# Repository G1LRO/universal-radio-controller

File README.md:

# universal-radio-controller
Open Hardware elements of the G1LRO Universal Radio Controller.

Refer to www.g1lro.uk for technical and electronic interface specifications

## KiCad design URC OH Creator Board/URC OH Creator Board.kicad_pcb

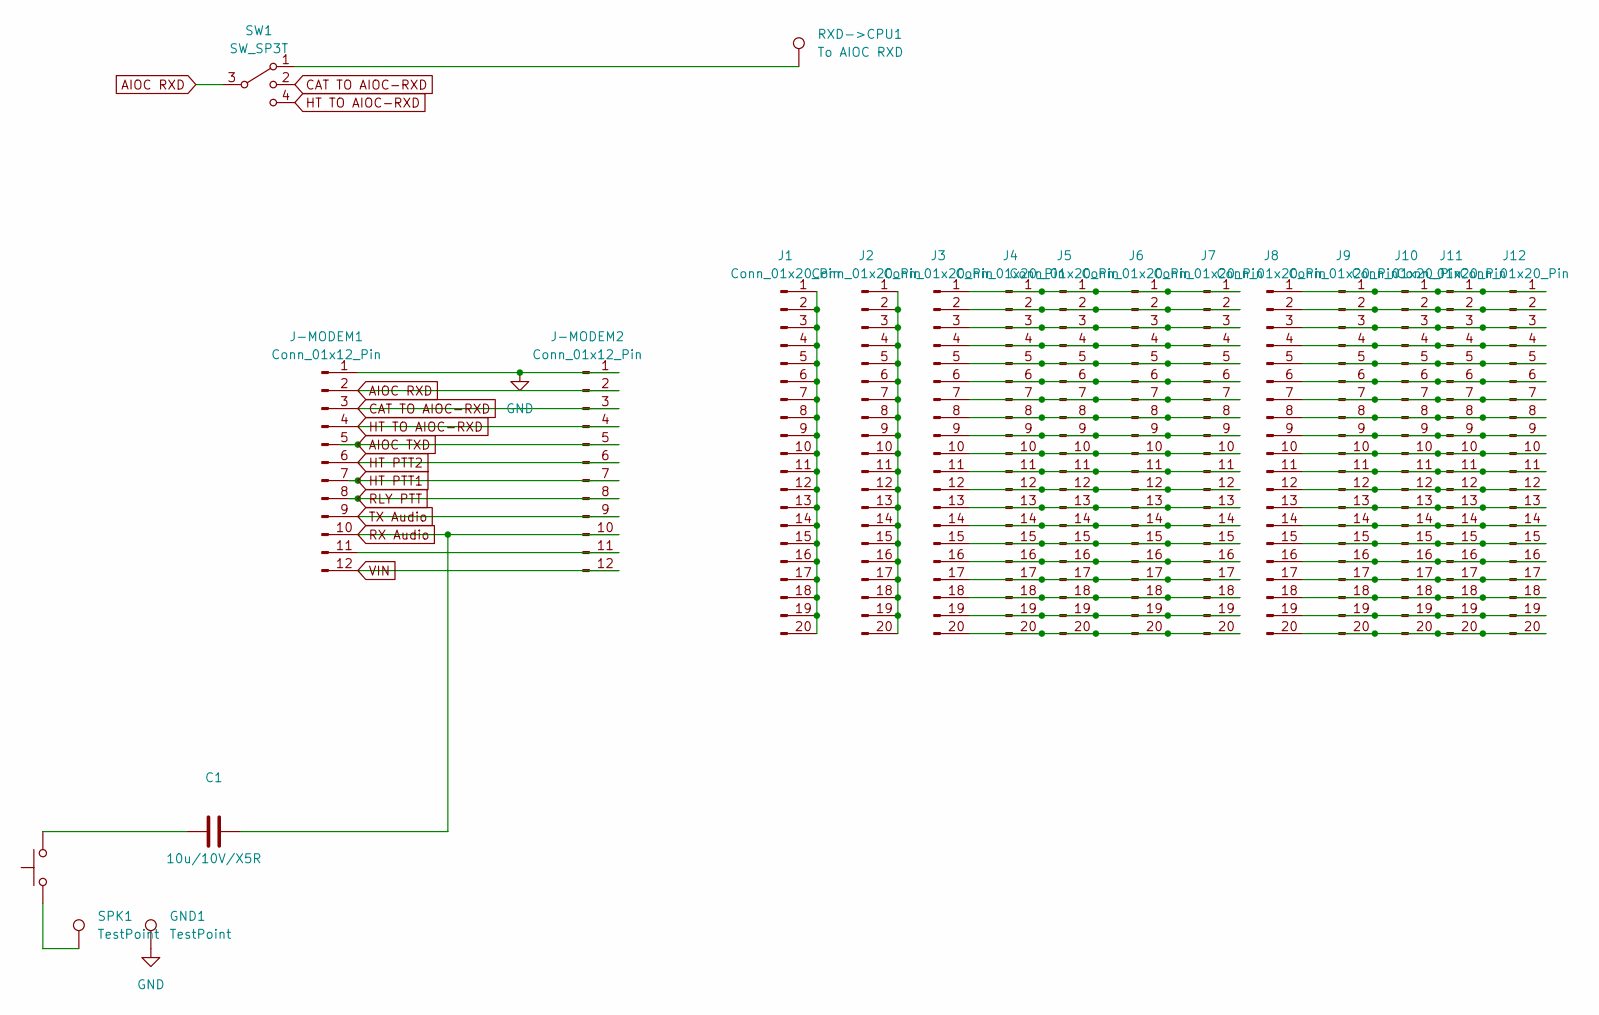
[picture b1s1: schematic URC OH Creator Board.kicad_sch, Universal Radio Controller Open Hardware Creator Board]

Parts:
C1: 10u/10V/X5R; C_0603_1608Metric; LCSC C19702
GND1: TestPoint; TestPoint_Pad_3.0x3.0mm
J1, J2, J3, J4, J5, J6, J7, J8, J9, J10, J11, J12: Conn_01x20_Pin; PinSocket_1x20_P2.54mm_Vertical; LCSC DNP
J-MODEM1, J-MODEM2: Conn_01x12_Pin; PinSocket_1x12_P2.54mm_Vertical; LCSC DNP
RXD->CPU1: To AIOC RXD; TestPoint_THTPad_1.5x1.5mm_Drill0.7mm
SPK1: TestPoint; TestPoint_Pad_3.0x3.0mm
SW1: SW_SP3T; SW_TPDT_THT-5mm; LCSC C393948
SW2: SW Monitor; SW_Tactile_SPST_Angled_C2689823; LCSC C2689823

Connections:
AIOC RXD: J-MODEM1.2, J-MODEM2.2, SW1.3
AIOC TXD: J-MODEM1.5, J-MODEM2.5
CAT TO AIOC-RXD: J-MODEM1.3, J-MODEM2.3, SW1.2
GND: GND1.1, J-MODEM1.1, J-MODEM2.1
HT PTT1: J-MODEM1.7, J-MODEM2.7
HT PTT2: J-MODEM1.6, J-MODEM2.6
HT TO AIOC-RXD: J-MODEM1.4, J-MODEM2.4, SW1.4
unnamed: C1.1, SW2.2
unnamed: J1.1, J1.2, J1.3, J1.4, J1.5, J1.6, J1.7, J1.8, J1.9, J1.10, J1.11, J1.12, J1.13, J1.14, J1.15, J1.16, J1.17, J1.18, J1.19, J1.20
unnamed: J2.1, J2.2, J2.3, J2.4, J2.5, J2.6, J2.7, J2.8, J2.9, J2.10, J2.11, J2.12, J2.13, J2.14, J2.15, J2.16, J2.17, J2.18, J2.19, J2.20
unnamed: J3.1, J4.1, J5.1, J6.1, J7.1
unnamed: J3.2, J4.2, J5.2, J6.2, J7.2
unnamed: J3.3, J4.3, J5.3, J6.3, J7.3
unnamed: J3.4, J4.4, J5.4, J6.4, J7.4
unnamed: J3.5, J4.5, J5.5, J6.5, J7.5
unnamed: J3.6, J4.6, J5.6, J6.6, J7.6
unnamed: J3.7, J4.7, J5.7, J6.7, J7.7
unnamed: J3.8, J4.8, J5.8, J6.8, J7.8
unnamed: J3.9, J4.9, J5.9, J6.9, J7.9
unnamed: J3.10, J4.10, J5.10, J6.10, J7.10
unnamed: J3.11, J4.11, J5.11, J6.11, J7.11
unnamed: J3.12, J4.12, J5.12, J6.12, J7.12
unnamed: J3.13, J4.13, J5.13, J6.13, J7.13
unnamed: J3.14, J4.14, J5.14, J6.14, J7.14
unnamed: J3.15, J4.15, J5.15, J6.15, J7.15
unnamed: J3.16, J4.16, J5.16, J6.16, J7.16
unnamed: J3.17, J4.17, J5.17, J6.17, J7.17
unnamed: J3.18, J4.18, J5.18, J6.18, J7.18
unnamed: J3.19, J4.19, J5.19, J6.19, J7.19
unnamed: J3.20, J4.20, J5.20, J6.20, J7.20
unnamed: J8.1, J9.1, J10.1, J11.1, J12.1
unnamed: J8.2, J9.2, J10.2, J11.2, J12.2
unnamed: J8.3, J9.3, J10.3, J11.3, J12.3
unnamed: J8.4, J9.4, J10.4, J11.4, J12.4
unnamed: J8.5, J9.5, J10.5, J11.5, J12.5
unnamed: J8.6, J9.6, J10.6, J11.6, J12.6
unnamed: J8.7, J9.7, J10.7, J11.7, J12.7
unnamed: J8.8, J9.8, J10.8, J11.8, J12.8
unnamed: J8.9, J9.9, J10.9, J11.9, J12.9
unnamed: J8.10, J9.10, J10.10, J11.10, J12.10
unnamed: J8.11, J9.11, J10.11, J11.11, J12.11
unnamed: J8.12, J9.12, J10.12, J11.12, J12.12
unnamed: J8.13, J9.13, J10.13, J11.13, J12.13
unnamed: J8.14, J9.14, J10.14, J11.14, J12.14
unnamed: J8.15, J9.15, J10.15, J11.15, J12.15
unnamed: J8.16, J9.16, J10.16, J11.16, J12.16
unnamed: J8.17, J9.17, J10.17, J11.17, J12.17
unnamed: J8.18, J9.18, J10.18, J11.18, J12.18
unnamed: J8.19, J9.19, J10.19, J11.19, J12.19
unnamed: J8.20, J9.20, J10.20, J11.20, J12.20
unnamed: J-MODEM1.11, J-MODEM2.11
unnamed: RXD->CPU1.1, SW1.1
unnamed: SPK1.1, SW2.1
RLY PTT: J-MODEM1.8, J-MODEM2.8
RX Audio: C1.2, J-MODEM1.10, J-MODEM2.10
TX Audio: J-MODEM1.9, J-MODEM2.9
VIN: J-MODEM1.12, J-MODEM2.12

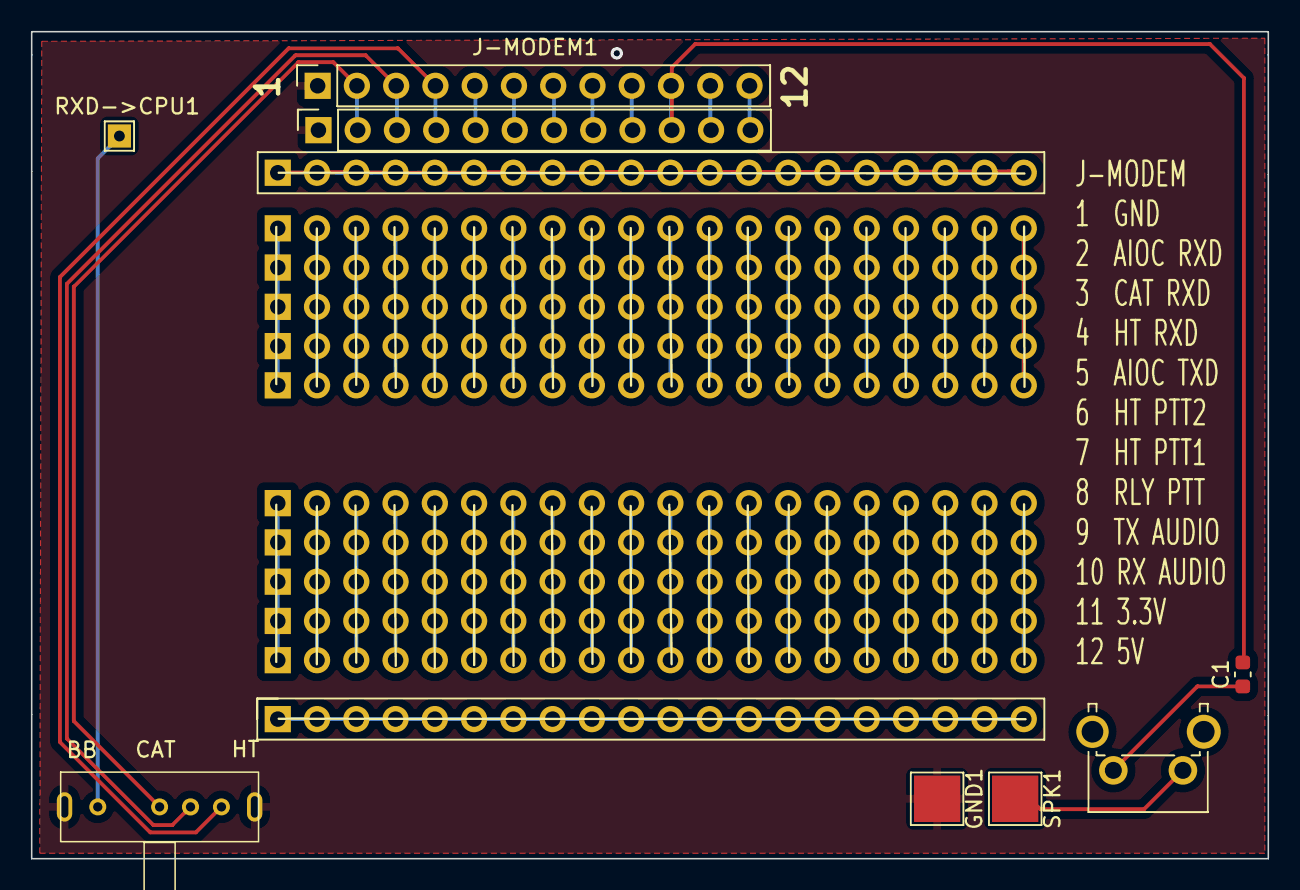
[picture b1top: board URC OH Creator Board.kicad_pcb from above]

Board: 2 copper layers, 80.0 x 53.5 mm, 20 parts (0 on the bottom side), 57 nets.

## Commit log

2024-01-03 Initial Kcad file commit
2024-01-03 added board edge locks
2024-01-03 locked switch location
2024-01-27 Changed speaker series resistor to 10uF capacitor

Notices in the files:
URC OH Creator Board/URC OH Creator Board.kicad_pcb:
MIT License
Copyright (c) 2024 G1LRO
Copyright (c)
